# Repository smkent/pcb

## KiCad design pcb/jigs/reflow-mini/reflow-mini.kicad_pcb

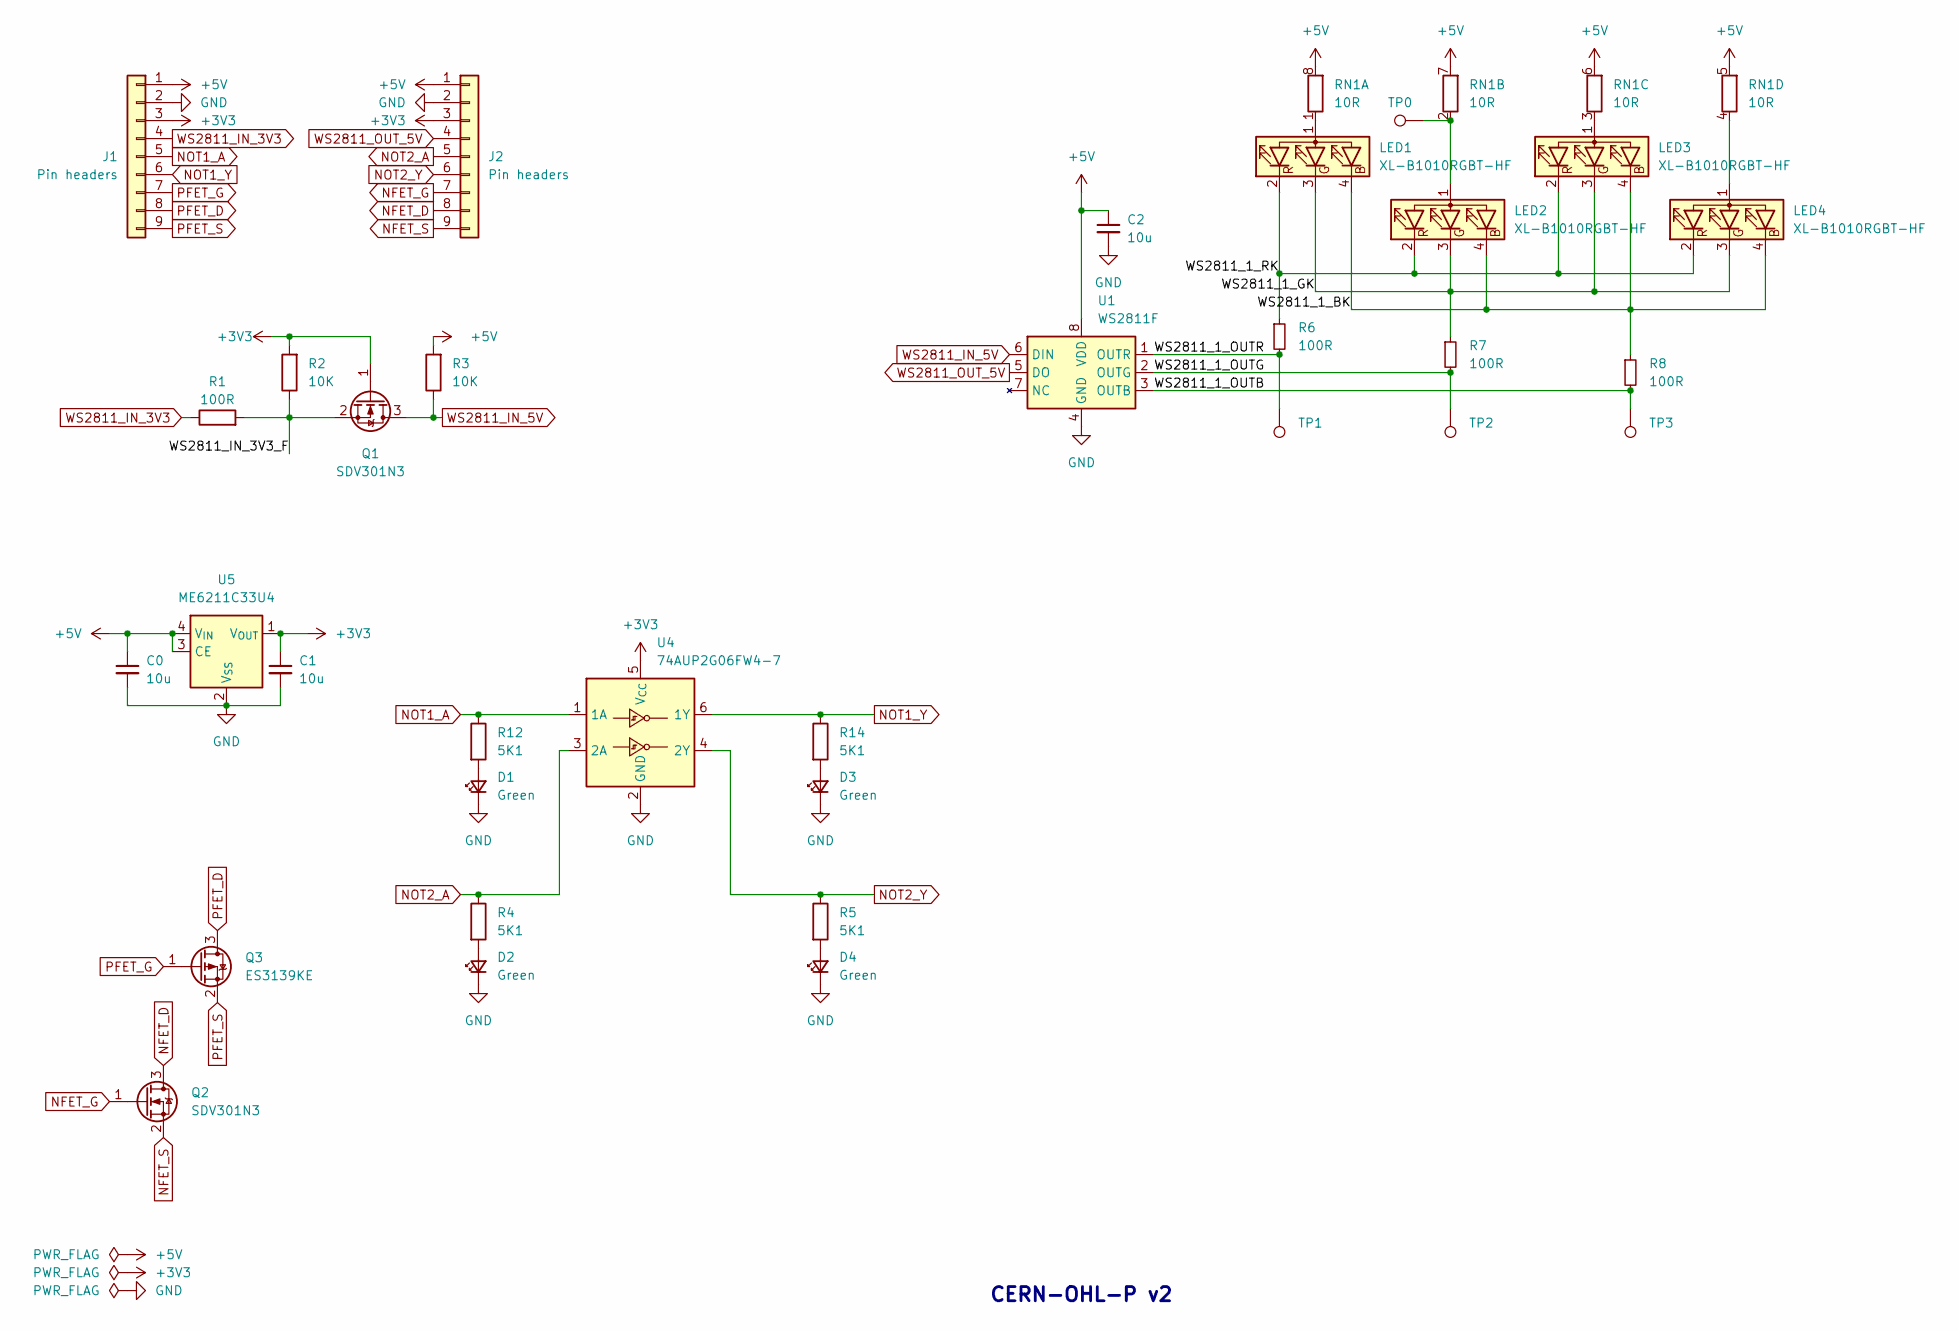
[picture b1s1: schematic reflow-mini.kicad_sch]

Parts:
C0, C1, C2: 10u; C_0402_1005Metric
D1, D2, D3, D4: Green; LED_0402_1005Metric
J1, J2: Pin headers; PinHeader_1x09_P2.54mm_Vertical_simple
LED1, LED2, LED3, LED4: XL-B1010RGBT-HF; LED_RGB_XL-B1010RGBT-HF_1.0x1.0mm; LCSC Part C22464515
Q1, Q2: SDV301N3; DFN1006-3; LCSC Part C5334596
Q3: ES3139KE; DFN1006-3; LCSC Part C7527987
R1: 100R; R_0402_1005Metric
R2, R3: 10K; R_0402_1005Metric
R4, R5, R12, R14: 5K1; R_0402_1005Metric
R6, R7, R8: 100R; R_0603_1608Metric
RN1: 10R; R_Array_Convex_4x0603
TP0, TP1, TP2, TP3: TestPoint; TestPoint_Pad_D1.0mm
U1: WS2811F; FSOP-8_3.3x1.7mm_P0.80mm; LCSC Part C5446692
U4: 74AUP2G06FW4-7; X2-DFN1010-6_L1.0-W1.0-P0.35-BL; LCSC Part C842402
U5: ME6211C33U4; UDFN-4-1EP_1x1mm_P0.65mm_EP0.48x0.48mm; LCSC Part C428904

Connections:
+3V3: C1.1, J1.3, J2.3, Q1.1 (G), R2.2, U4.5 (V_{CC}), U5.1 (V_{OUT})
+5V: C0.1, C2.1, J1.1, J2.1, R3.2, RN1.5 (R4.2), RN1.6 (R3.2), RN1.7 (R2.2), RN1.8 (R1.2), U1.8 (VDD), U5.3 (CE), U5.4 (V_{IN})
/WS2811_1_BK: LED1.4 (BK), LED2.4 (BK), LED3.4 (BK), LED4.4 (BK), R8.1
/WS2811_1_GK: LED1.3 (GK), LED2.3 (GK), LED3.3 (GK), LED4.3 (GK), R7.1
/WS2811_1_OUTB: R8.2, TP3.1, U1.3 (OUTB)
/WS2811_1_OUTG: R7.2, TP2.1, U1.2 (OUTG)
/WS2811_1_OUTR: R6.2, TP1.1, U1.1 (OUTR)
/WS2811_1_RK: LED1.2 (RK), LED2.2 (RK), LED3.2 (RK), LED4.2 (RK), R6.1
/WS2811_IN_3V3_F: Q1.2 (S), R1.2, R2.1
GND: C0.2, C1.2, C2.2, D1.1 (K), D2.1 (K), D3.1 (K), D4.1 (K), J1.2, J2.2, U1.4 (GND), U4.2 (GND), U5.2 (V_{SS})
NFET_D: J2.8, Q2.3 (D)
NFET_G: J2.7, Q2.1 (G)
NFET_S: J2.9, Q2.2 (S)
NOT1_A: J1.5, R12.1, U4.1 (1A)
NOT1_Y: J1.6, R14.1, U4.6 (1Y)
NOT2_A: J2.5, R4.1, U4.3 (2A)
NOT2_Y: J2.6, R5.1, U4.4 (2Y)
unnamed: D1.2 (A), R12.2
unnamed: D2.2 (A), R4.2
unnamed: D3.2 (A), R14.2
unnamed: D4.2 (A), R5.2
unnamed: LED1.1 (A), RN1.1 (R1.1)
unnamed: LED2.1 (A), RN1.2 (R2.1), TP0.1
unnamed: LED3.1 (A), RN1.3 (R3.1)
unnamed: LED4.1 (A), RN1.4 (R4.1)
PFET_D: J1.8, Q3.3 (D)
PFET_G: J1.7, Q3.1 (G)
PFET_S: J1.9, Q3.2 (S)
WS2811_IN_3V3: J1.4, R1.1
WS2811_IN_5V: Q1.3 (D), R3.1, U1.6 (DIN)
WS2811_OUT_5V: J2.4, U1.5 (DO)

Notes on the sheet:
CERN-OHL-P v2

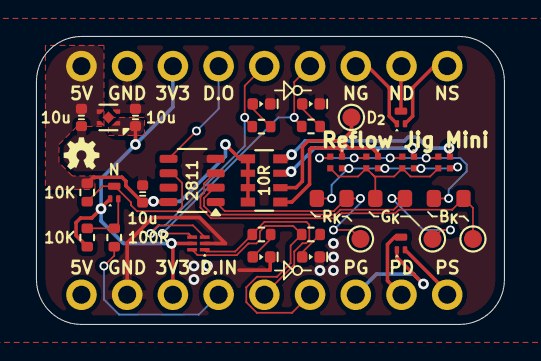
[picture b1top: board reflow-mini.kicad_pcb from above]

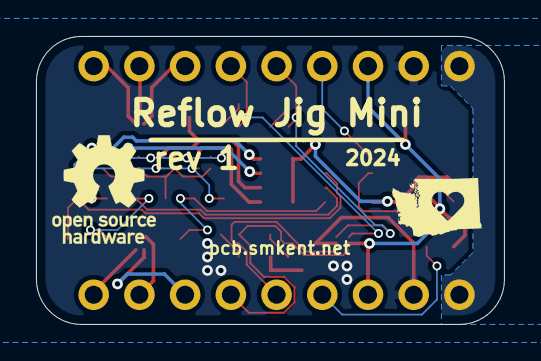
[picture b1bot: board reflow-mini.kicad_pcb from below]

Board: 2 copper layers, 26.0 x 16.0 mm, 34 parts (2 on the bottom side), 31 nets.

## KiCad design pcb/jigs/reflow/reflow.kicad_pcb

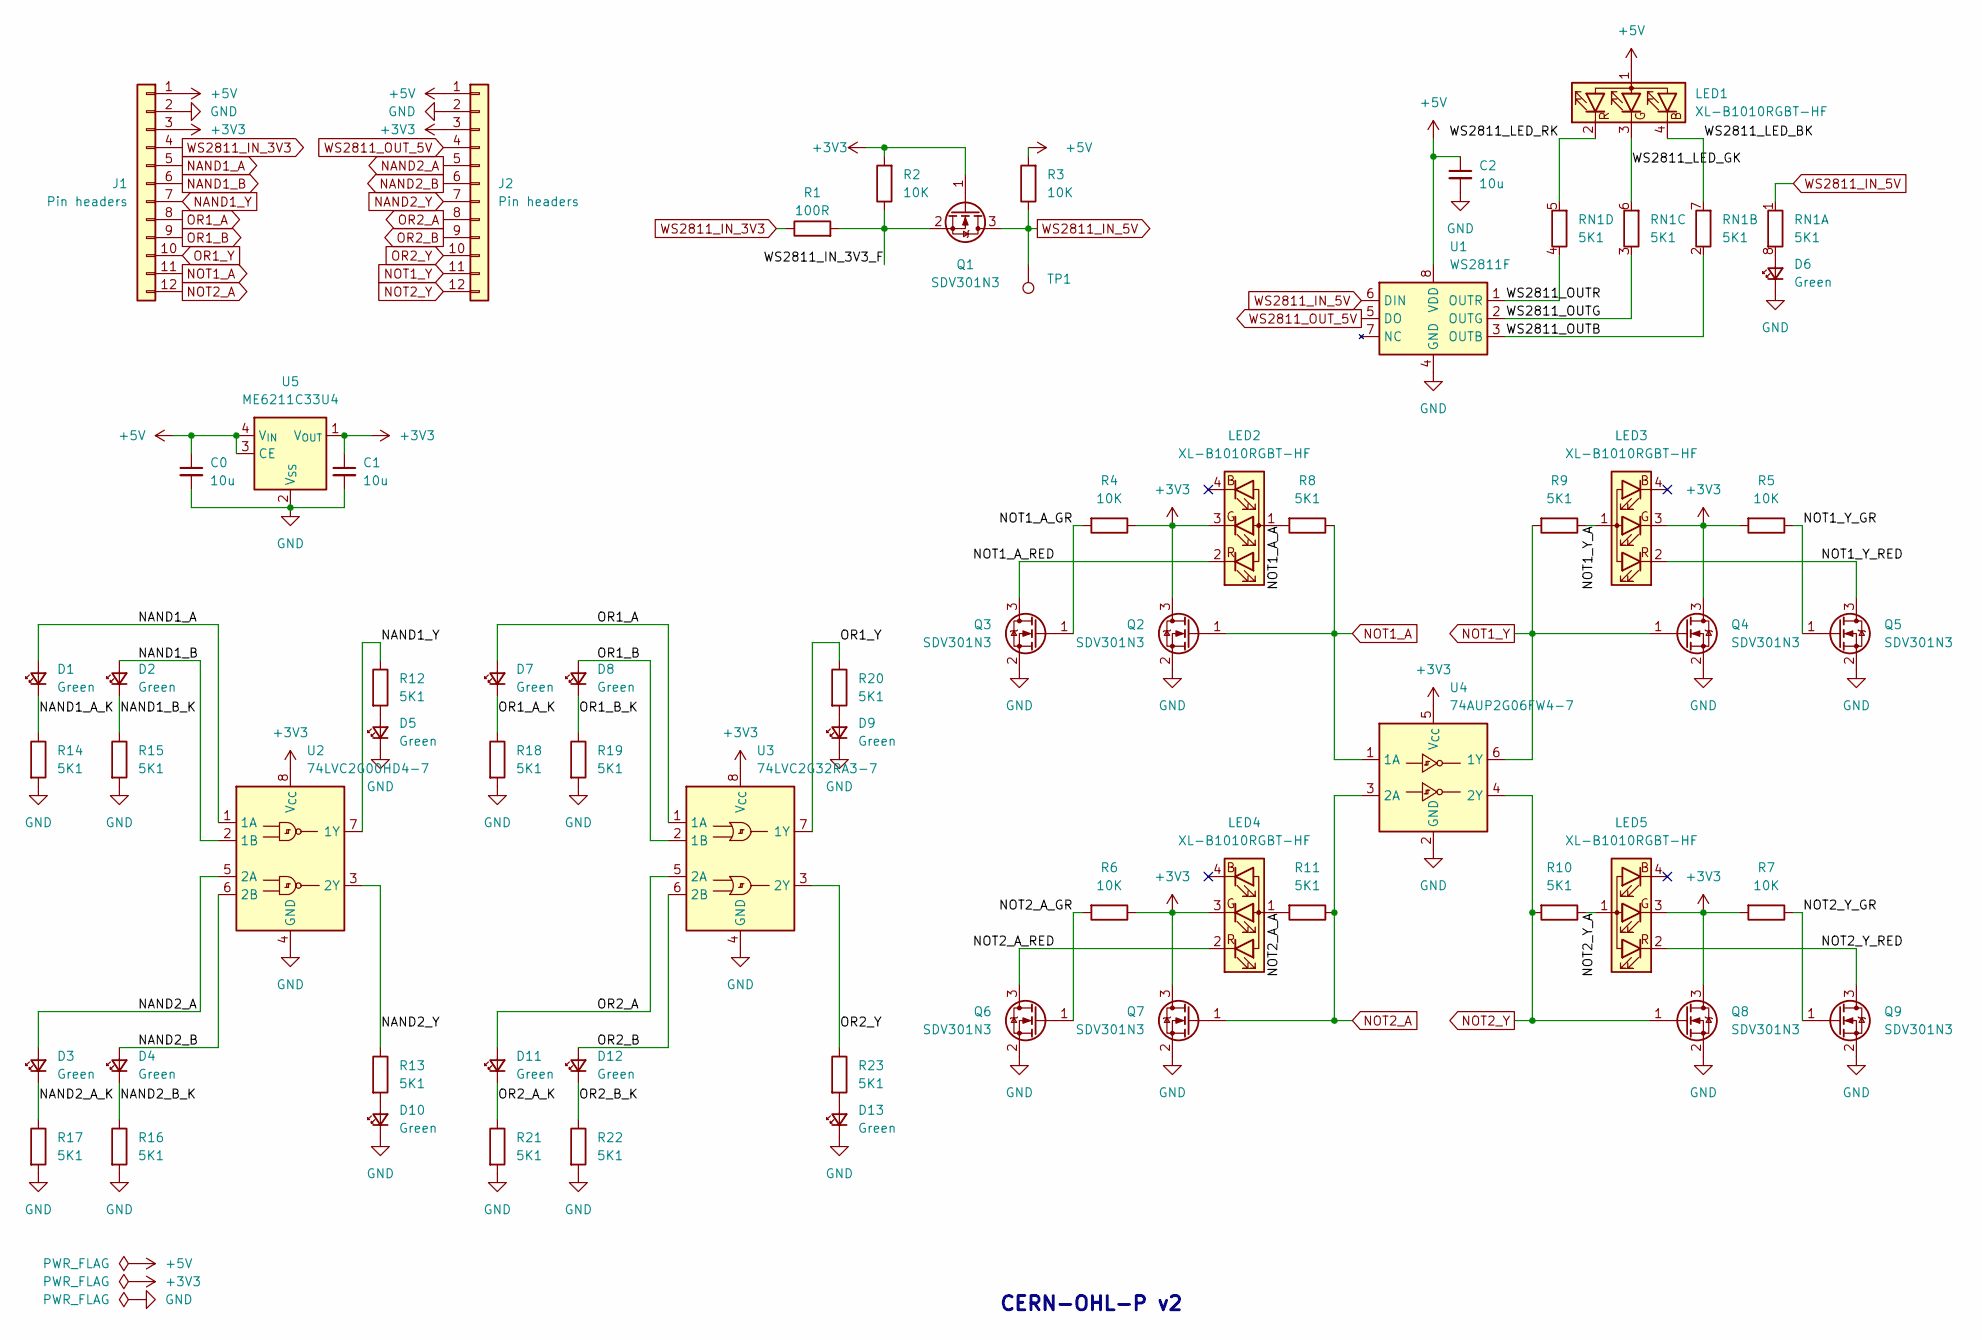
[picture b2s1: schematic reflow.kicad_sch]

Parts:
C0, C1, C2: 10u; C_0402_1005Metric
D1, D2, D3, D4, D5, D6, D7, D8, D9, D10, D11, D12, D13: Green; LED_0402_1005Metric
J1, J2: Pin headers; PinHeader_1x12_P2.54mm_Vertical_simple_pad2gnd
LED1, LED2, LED3, LED4, LED5: XL-B1010RGBT-HF; LED_RGB_XL-B1010RGBT-HF_1.0x1.0mm; LCSC Part C22464515
Q1, Q2, Q3, Q4, Q5, Q6, Q7, Q8, Q9: SDV301N3; DFN1006-3; LCSC Part C5334596
R1: 100R; R_0402_1005Metric
R2, R3, R4, R5, R6, R7: 10K; R_0402_1005Metric
R8, R9, R10, R11, R12, R13, R14, R15, R16, R17, R18, R19, R20, R21, R22, R23: 5K1; R_0402_1005Metric
RN1: 5K1; R_Array_Convex_4x0402
TP1: TestPoint; TestPoint_Pad_D1.0mm
U1: WS2811F; FSOP-8_3.3x1.7mm_P0.80mm; LCSC Part C5446692
U2: 74LVC2G00HD4-7; X2-DFN2010-8_L2.0-W1.0-P0.50-BL; LCSC Part C842639
U3: 74LVC2G32RA3-7; X2-DFN1210-8_L1.2-W1.0-P0.30-BL; LCSC Part C842616
U4: 74AUP2G06FW4-7; X2-DFN1010-6_L1.0-W1.0-P0.35-BL; LCSC Part C842402
U5: ME6211C33U4; UDFN-4-1EP_1x1mm_P0.65mm_EP0.48x0.48mm; LCSC Part C428904

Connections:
+3V3: C1.1, J1.3, J2.3, LED2.3 (GK), LED3.3 (GK), LED4.3 (GK), LED5.3 (GK), Q1.1 (G), Q2.3 (D), Q4.3 (D), Q7.3 (D), Q8.3 (D), R2.2, R4.1, R5.2, R6.1, R7.2, U2.8 (V_{CC}), U3.8 (V_{CC}), U4.5 (V_{CC}), U5.1 (V_{OUT})
+5V: C0.1, C2.1, J1.1, J2.1, LED1.1 (A), R3.2, U1.8 (VDD), U5.3 (CE), U5.4 (V_{IN})
/NAND1_A_K: D1.1 (K), R14.1
/NAND1_B_K: D2.1 (K), R15.1
/NAND2_A_K: D3.1 (K), R17.1
/NAND2_B_K: D4.1 (K), R16.1
/NOT1_A_A: LED2.1 (A), R8.2
/NOT1_A_GR: Q3.1 (G), R4.2
/NOT1_A_RED: LED2.2 (RK), Q3.3 (D)
/NOT1_Y_A: LED3.1 (A), R9.1
/NOT1_Y_GR: Q5.1 (G), R5.1
/NOT1_Y_RED: LED3.2 (RK), Q5.3 (D)
/NOT2_A_A: LED4.1 (A), R11.2
/NOT2_A_GR: Q6.1 (G), R6.2
/NOT2_A_RED: LED4.2 (RK), Q6.3 (D)
/NOT2_Y_A: LED5.1 (A), R10.1
/NOT2_Y_GR: Q9.1 (G), R7.1
/NOT2_Y_RED: LED5.2 (RK), Q9.3 (D)
/OR1_A_K: D7.1 (K), R18.1
/OR1_B_K: D8.1 (K), R19.1
/OR2_A_K: D11.1 (K), R21.1
/OR2_B_K: D12.1 (K), R22.1
/WS2811_IN_3V3_F: Q1.2 (S), R1.2, R2.1
/WS2811_LED_BK: LED1.4 (BK), RN1.7 (R2.2)
/WS2811_LED_GK: LED1.3 (GK), RN1.6 (R3.2)
/WS2811_LED_RK: LED1.2 (RK), RN1.5 (R4.2)
/WS2811_OUTB: RN1.2 (R2.1), U1.3 (OUTB)
/WS2811_OUTG: RN1.3 (R3.1), U1.2 (OUTG)
/WS2811_OUTR: RN1.4 (R4.1), U1.1 (OUTR)
GND: C0.2, C1.2, C2.2, D5.1 (K), D6.1 (K), D9.1 (K), D10.1 (K), D13.1 (K), J1.2, J2.2, Q2.2 (S), Q3.2 (S), Q4.2 (S), Q5.2 (S), Q6.2 (S), Q7.2 (S), Q8.2 (S), Q9.2 (S), R14.2, R15.2, R16.2, R17.2, R18.2, R19.2, R21.2, R22.2, U1.4 (GND), U2.4 (GND), U3.4 (GND), U4.2 (GND), U5.2 (V_{SS})
NAND1_A: D1.2 (A), J1.5, U2.1 (1A)
NAND1_B: D2.2 (A), J1.6, U2.2 (1B)
NAND1_Y: J1.7, R12.1, U2.7 (1Y)
NAND2_A: D3.2 (A), J2.5, U2.5 (2A)
NAND2_B: D4.2 (A), J2.6, U2.6 (2B)
NAND2_Y: J2.7, R13.1, U2.3 (2Y)
NOT1_A: J1.11, Q2.1 (G), R8.1, U4.1 (1A)
NOT1_Y: J2.11, Q4.1 (G), R9.2, U4.6 (1Y)
NOT2_A: J1.12, Q7.1 (G), R11.1, U4.3 (2A)
NOT2_Y: J2.12, Q8.1 (G), R10.2, U4.4 (2Y)
unnamed: D5.2 (A), R12.2
unnamed: D6.2 (A), RN1.8 (R1.2)
unnamed: D9.2 (A), R20.2
unnamed: D10.2 (A), R13.2
unnamed: D13.2 (A), R23.2
OR1_A: D7.2 (A), J1.8, U3.1 (1A)
OR1_B: D8.2 (A), J1.9, U3.2 (1B)
OR1_Y: J1.10, R20.1, U3.7 (1Y)
OR2_A: D11.2 (A), J2.8, U3.5 (2A)
OR2_B: D12.2 (A), J2.9, U3.6 (2B)
OR2_Y: J2.10, R23.1, U3.3 (2Y)
WS2811_IN_3V3: J1.4, R1.1
WS2811_IN_5V: Q1.3 (D), R3.1, RN1.1 (R1.1), TP1.1, U1.6 (DIN)
WS2811_OUT_5V: J2.4, U1.5 (DO)

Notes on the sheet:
CERN-OHL-P v2

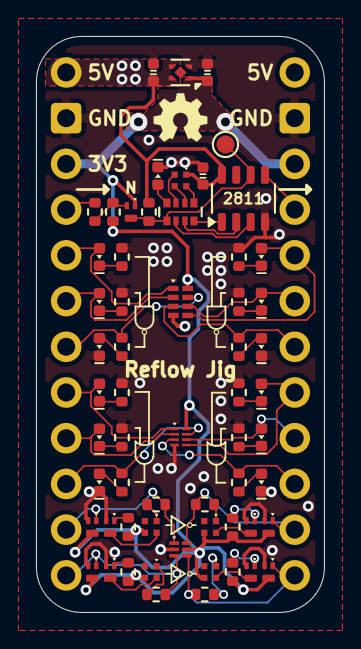
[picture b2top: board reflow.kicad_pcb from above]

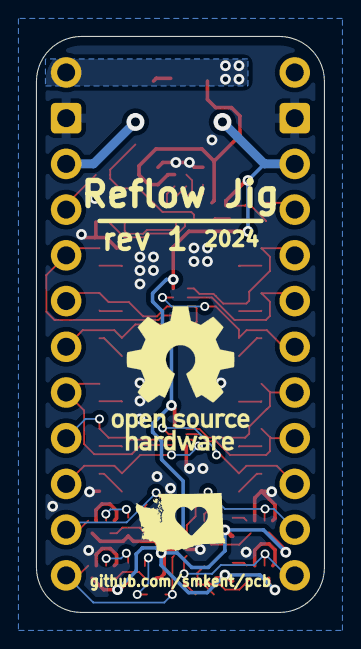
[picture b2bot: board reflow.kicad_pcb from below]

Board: 2 copper layers, 16.0 x 32.0 mm, 62 parts (2 on the bottom side), 54 nets.

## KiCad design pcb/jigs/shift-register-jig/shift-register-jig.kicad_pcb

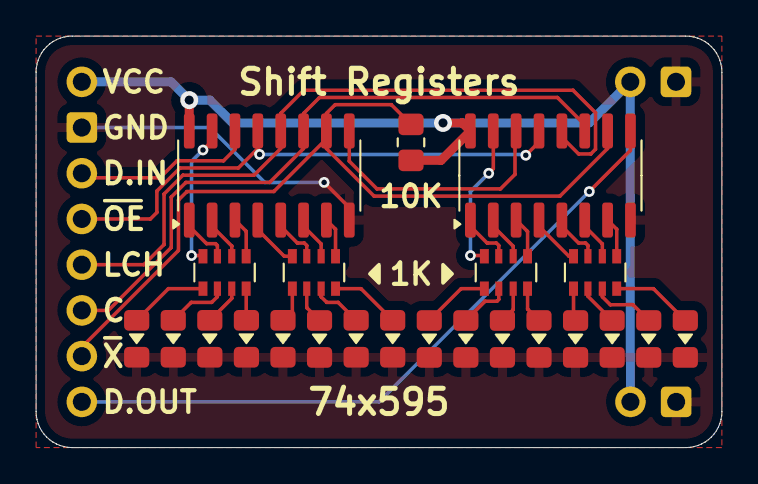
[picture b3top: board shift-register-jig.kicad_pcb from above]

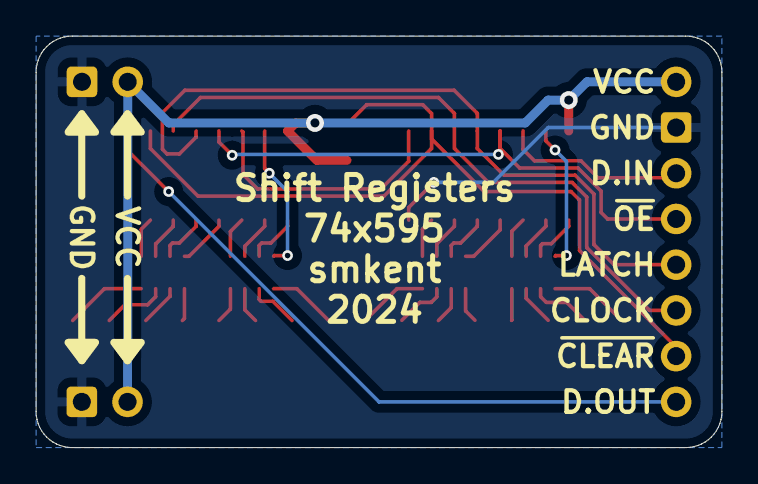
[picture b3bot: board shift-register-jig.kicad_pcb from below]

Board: 2 copper layers, 38.1 x 22.9 mm, 26 parts (3 on the bottom side), 41 nets.

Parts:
J1, J5: Conn_01x02; PinHeader_1x02_P2.54mm_Vertical_simple_pad2gnd
J2: Conn_01x08; PinHeader_1x08_P2.54mm_Vertical_simple_pad2gnd
LED1, LED2, LED3, LED4, LED5, LED6, LED7, LED8, LED9, LED10, LED11, LED12, LED13, LED14, LED15, LED16: LED; LED_0805_2012Metric_Pad1.15x1.40mm_HandSolder_simple
R1: 10K; R_0805_2012Metric_Pad1.20x1.40mm_HandSolder
RN1, RN2, RN3, RN4: 1K; R_Array_Convex_4x0603
U1, U2: 74HC595; SOIC-16_3.9x9.9mm_P1.27mm

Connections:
Clear: J2.7, R1.2, U1.10 (~SRCLR), U2.10 (~SRCLR)
Clock: J2.6, U1.11 (SRCLK), U2.11 (SRCLK)
Data: J2.3, U1.14 (SER)
Data2: U1.9 (QH'), U2.14 (SER)
Data_Out: J2.8, U2.9 (QH')
GND: J1.2, J2.2, J5.2, LED1.1 (K), LED2.1 (K), LED3.1 (K), LED4.1 (K), LED5.1 (K), LED6.1 (K), LED7.1 (K), LED8.1 (K), LED9.1 (K), LED10.1 (K), LED11.1 (K), LED12.1 (K), LED13.1 (K), LED14.1 (K), LED15.1 (K), LED16.1 (K), U1.8 (GND), U2.8 (GND)
LED1: RN1.8 (R1.2), U1.15 (QA)
LED2: RN1.7 (R2.2), U1.1 (QB)
LED3: RN1.6 (R3.2), U1.2 (QC)
LED4: RN1.5 (R4.2), U1.3 (QD)
LED5: RN2.8 (R1.2), U1.4 (QE)
LED6: RN2.7 (R2.2), U1.5 (QF)
LED7: RN2.6 (R3.2), U1.6 (QG)
LED8: RN2.5 (R4.2), U1.7 (QH)
LED9: RN3.8 (R1.2), U2.15 (QA)
LED10: RN3.7 (R2.2), U2.1 (QB)
LED11: RN3.6 (R3.2), U2.2 (QC)
LED12: RN3.5 (R4.2), U2.3 (QD)
LED13: RN4.8 (R1.2), U2.4 (QE)
LED14: RN4.7 (R2.2), U2.5 (QF)
LED15: RN4.6 (R3.2), U2.6 (QG)
LED16: RN4.5 (R4.2), U2.7 (QH)
Latch: J2.5, U1.12 (RCLK), U2.12 (RCLK)
unnamed: LED1.2 (A), RN1.1 (R1.1)
unnamed: LED2.2 (A), RN1.2 (R2.1)
unnamed: LED3.2 (A), RN1.3 (R3.1)
unnamed: LED4.2 (A), RN1.4 (R4.1)
unnamed: LED5.2 (A), RN2.1 (R1.1)
unnamed: LED6.2 (A), RN2.2 (R2.1)
unnamed: LED7.2 (A), RN2.3 (R3.1)
unnamed: LED8.2 (A), RN2.4 (R4.1)
unnamed: LED9.2 (A), RN3.1 (R1.1)
unnamed: LED10.2 (A), RN3.2 (R2.1)
unnamed: LED11.2 (A), RN3.3 (R3.1)
unnamed: LED12.2 (A), RN3.4 (R4.1)
unnamed: LED13.2 (A), RN4.1 (R1.1)
unnamed: LED14.2 (A), RN4.2 (R2.1)
unnamed: LED15.2 (A), RN4.3 (R3.1)
unnamed: LED16.2 (A), RN4.4 (R4.1)
OE: J2.4, U1.13 (~OE), U2.13 (~OE)
VCC: J1.1, J2.1, J5.1, R1.1, U1.16 (VCC), U2.16 (VCC)

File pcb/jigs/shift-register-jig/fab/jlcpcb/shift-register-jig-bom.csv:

Comment,Designator,Footprint,LCSC
LED,"LED1,LED2,LED3,LED4,LED5,LED6,LED7,LED8,LED9,LED10,LED11,LED12,LED13,LED14,LED15,LED16",custom:LED_0805_2012Metric_Pad1.15x1.40mm_HandSolder_simple,
Conn_01x02,"J1,J5",custom:PinHeader_1x02_P2.54mm_Vertical_simple_pad2gnd,
1K,"RN1,RN2,RN3,RN4",Resistor_SMD:R_Array_Convex_4x0603,
74HC595,"U1,U2",Package_SO:SOIC-16_3.9x9.9mm_P1.27mm,
10K,R1,Resistor_SMD:R_0805_2012Metric_Pad1.20x1.40mm_HandSolder,
Conn_01x08,J2,custom:PinHeader_1x08_P2.54mm_Vertical_simple_pad2gnd,

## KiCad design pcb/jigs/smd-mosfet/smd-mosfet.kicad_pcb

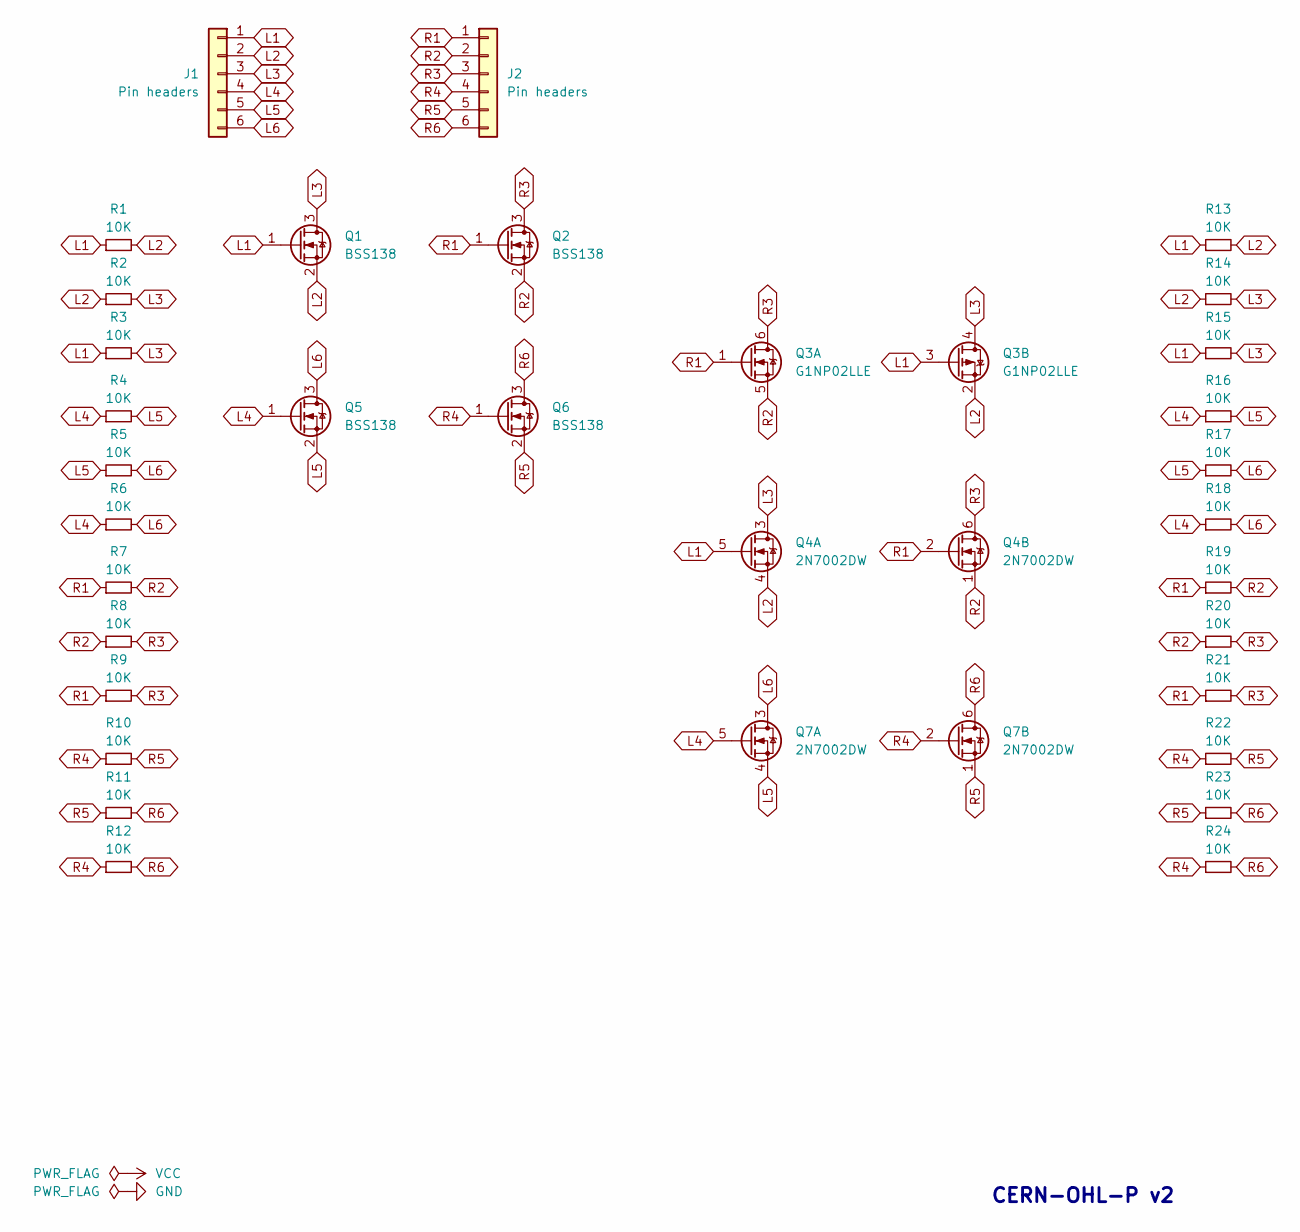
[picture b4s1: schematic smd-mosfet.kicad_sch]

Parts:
J1, J2: Pin headers; PinHeader_1x06_P2.54mm_Vertical_slim_simple
Q1, Q2, Q5, Q6: BSS138; SOT-23_mosfet
Q3: G1NP02LLE; SOT-23-6_G1NP02LLE_mosfet; LCSC Part C7465318
Q4, Q7: 2N7002DW; SOT-363_SC-70-6_mosfet; LCSC Part C5190214
R1, R2, R3, R4, R5, R6, R7, R8, R9, R10, R11, R12, R13, R14, R15, R16, R17, R18, R19, R20, R21, R22, R23, R24: 10K; R_0603_1608Metric_Pad0.98x0.95mm_HandSolder_simple

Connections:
L1: J1.1, Q1.1 (G), Q3.3 (G), Q4.5 (G), R1.1, R3.1, R13.1, R15.1
L2: J1.2, Q1.2 (S), Q3.2 (S), Q4.4 (S), R1.2, R2.1, R13.2, R14.1
L3: J1.3, Q1.3 (D), Q3.4 (D), Q4.3 (D), R2.2, R3.2, R14.2, R15.2
L4: J1.4, Q5.1 (G), Q7.5 (G), R4.1, R6.1, R16.1, R18.1
L5: J1.5, Q5.2 (S), Q7.4 (S), R4.2, R5.1, R16.2, R17.1
L6: J1.6, Q5.3 (D), Q7.3 (D), R5.2, R6.2, R17.2, R18.2
R1: J2.1, Q2.1 (G), Q3.1 (G), Q4.2 (G), R7.1, R9.1, R19.1, R21.1
R2: J2.2, Q2.2 (S), Q3.5 (S), Q4.1 (S), R7.2, R8.1, R19.2, R20.1
R3: J2.3, Q2.3 (D), Q3.6 (D), Q4.6 (D), R8.2, R9.2, R20.2, R21.2
R4: J2.4, Q6.1 (G), Q7.2 (G), R10.1, R12.1, R22.1, R24.1
R5: J2.5, Q6.2 (S), Q7.1 (S), R10.2, R11.1, R22.2, R23.1
R6: J2.6, Q6.3 (D), Q7.6 (D), R11.2, R12.2, R23.2, R24.2

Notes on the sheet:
CERN-OHL-P v2

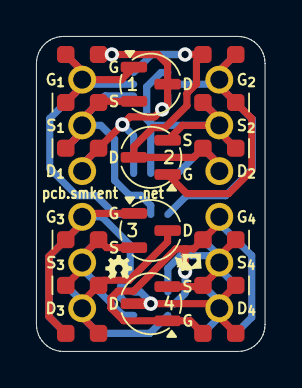
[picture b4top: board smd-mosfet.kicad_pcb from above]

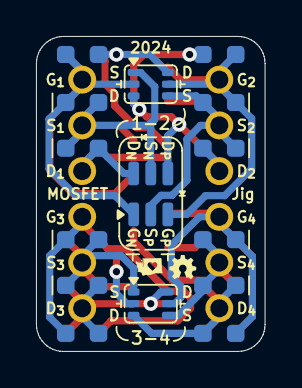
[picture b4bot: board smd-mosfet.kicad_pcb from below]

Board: 2 copper layers, 12.7 x 17.5 mm, 33 parts (17 on the bottom side), 12 nets.

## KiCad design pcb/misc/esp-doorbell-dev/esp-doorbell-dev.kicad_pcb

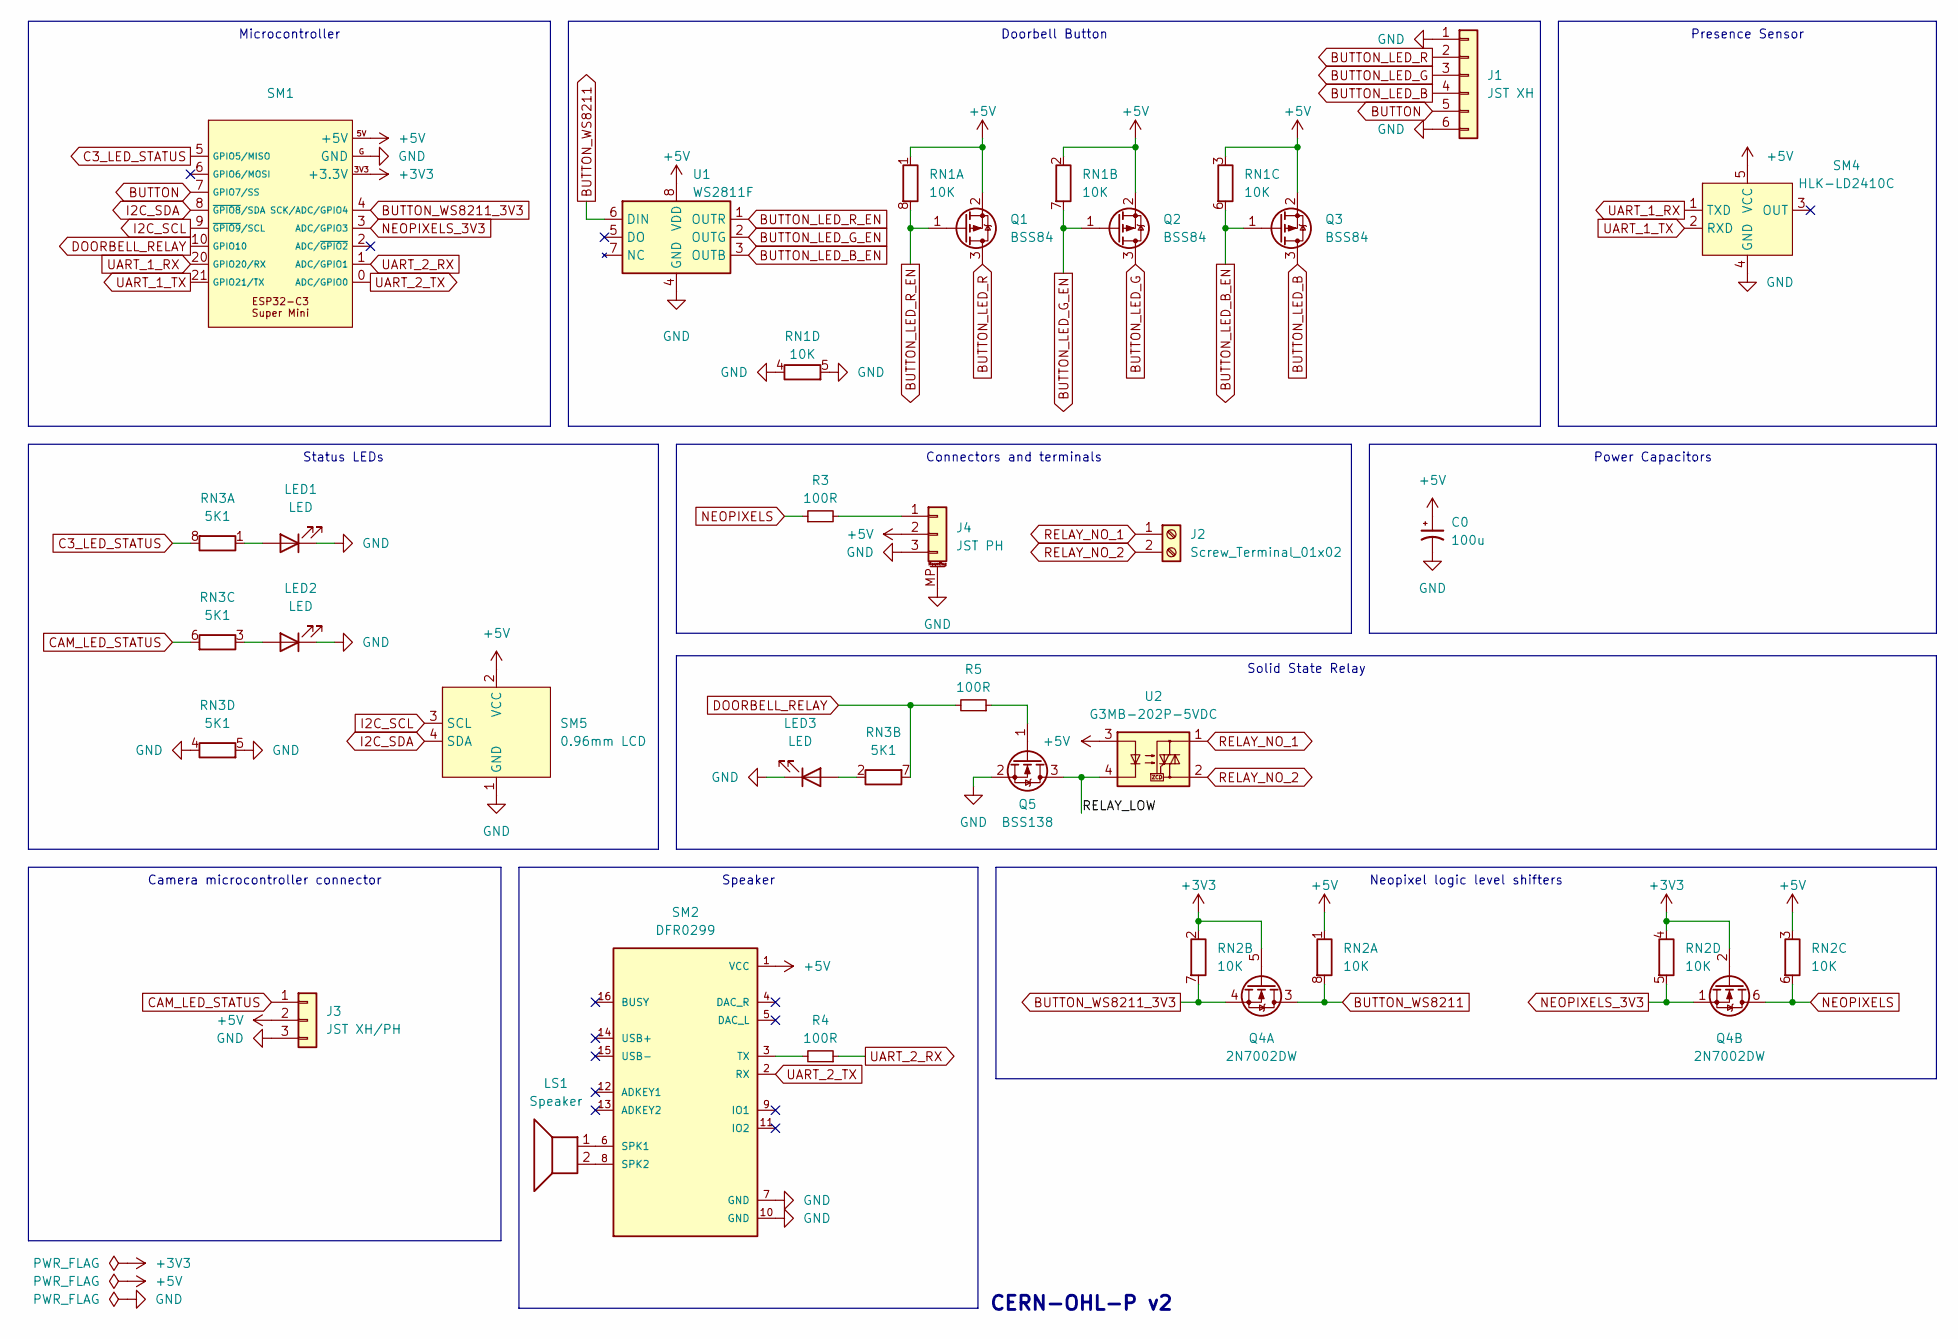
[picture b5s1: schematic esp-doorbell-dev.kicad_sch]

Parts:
C0: 100u; CP_Elec_5x5.4
J1: JST XH; JST_XH_S6B-XH-2AW_1x06_P2.50mm_Horizontal
J2: Screw_Terminal_01x02; TerminalBlock_Phoenix_PT-1,5-2-3.5-H_1x02_P3.50mm_Horizontal
J3: JST XH/PH; Conn_Combo_JST-1x03-XH_PH-THT
J4: JST PH; STEMMA-Signal-SMD-horizontal
LED1, LED2, LED3: LED; LED_0603_1608Metric_Pad1.05x0.95mm_HandSolder_simple
LS1: Speaker; Conn_Combo_JST-1x02-XH_PH-SMD-pad2gnd
Q1, Q2, Q3: BSS84; SOT-23
Q4: 2N7002DW; SOT-363_SC-70-6_HandSolder; LCSC Part C5190214
Q5: BSS138; SOT-23
R3, R4, R5: 100R; R_0603_1608Metric_Pad0.98x0.95mm_HandSolder
RN1, RN2: 10K; R_Array_Convex_4x0603
RN3: 5K1; R_Array_Convex_4x0603
SM1: ESP32-C3-Super-Mini-Pins
SM2: DFR0299; DFPlayer-Mini-DFR0299-module
SM4: HLK-LD2410C; HLK-LD2410C-module; LCSC Part C19723500
SM5: 0.96mm LCD; LCD-OLED-0.96-module-noholes; LCSC Part C7465997
U1: WS2811F; FSOP-8_3.3x1.7mm_P0.80mm; LCSC Part C5446692
U2: G3MB-202P-5VDC; Relay_G3MB-202P

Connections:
+3V3: Q4.2 (G), Q4.5 (G), RN2.2 (R2.1), RN2.4 (R4.1), SM1.3V3 (+3.3V)
+5V: C0.1, J3.2, J4.2, Q1.2 (S), Q2.2 (S), Q3.2 (S), RN1.1 (R1.1), RN1.2 (R2.1), RN1.3 (R3.1), RN2.1 (R1.1), RN2.3 (R3.1), SM1.5V (+5V), SM2.1 (VCC), SM4.5 (VCC), SM5.2 (VCC), U1.8 (VDD), U2.3
/RELAY_LOW: Q5.3 (D), U2.4
BUTTON: J1.5, SM1.7 (GPIO7/SS)
BUTTON_LED_B: J1.4, Q3.3 (D)
BUTTON_LED_B_EN: Q3.1 (G), RN1.6 (R3.2), U1.3 (OUTB)
BUTTON_LED_G: J1.3, Q2.3 (D)
BUTTON_LED_G_EN: Q2.1 (G), RN1.7 (R2.2), U1.2 (OUTG)
BUTTON_LED_R: J1.2, Q1.3 (D)
BUTTON_LED_R_EN: Q1.1 (G), RN1.8 (R1.2), U1.1 (OUTR)
BUTTON_WS8211: Q4.3 (D), RN2.8 (R1.2), U1.6 (DIN)
BUTTON_WS8211_3V3: Q4.4 (S), RN2.7 (R2.2), SM1.4 (SCK/ADC/GPIO4)
C3_LED_STATUS: RN3.8 (R1.2), SM1.5 (GPIO5/MISO)
CAM_LED_STATUS: J3.1, RN3.6 (R3.2)
DOORBELL_RELAY: R5.2, RN3.7 (R2.2), SM1.10 (GPIO10)
GND: C0.2, J1.1, J1.6, J3.3, J4.3, J4.MP (MountPin), LED1.1 (K), LED2.1 (K), LED3.1 (K), Q5.2 (S), RN1.4 (R4.1), RN1.5 (R4.2), RN3.4 (R4.1), RN3.5 (R4.2), SM1.G (GND), SM2.7 (GND), SM2.10 (GND), SM4.4 (GND), SM5.1 (GND), U1.4 (GND)
I2C_SCL: SM1.9 (~GPIO9/SCL), SM5.3 (SCL)
I2C_SDA: SM1.8 (~GPIO8/SDA), SM5.4 (SDA)
NEOPIXELS: Q4.6 (D), R3.1, RN2.6 (R3.2)
NEOPIXELS_3V3: Q4.1 (S), RN2.5 (R4.2), SM1.3 (ADC/GPIO3)
unnamed: J4.1, R3.2
unnamed: LED1.2 (A), RN3.1 (R1.1)
unnamed: LED2.2 (A), RN3.3 (R3.1)
unnamed: LED3.2 (A), RN3.2 (R2.1)
unnamed: Q5.1 (G), R5.1
unnamed: LS1.1, SM2.6 (SPK1)
unnamed: LS1.2, SM2.8 (SPK2)
unnamed: R4.2, SM2.3 (TX)
RELAY_NO_1: J2.1, U2.1
RELAY_NO_2: J2.2, U2.2
UART_1_RX: SM1.20 (GPIO20/RX), SM4.1 (TXD)
UART_1_TX: SM1.21 (GPIO21/TX), SM4.2 (RXD)
UART_2_RX: R4.1, SM1.1 (ADC/GPIO1)
UART_2_TX: SM1.0 (ADC/GPIO0), SM2.2 (RX)

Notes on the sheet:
Microcontroller
Doorbell Button
Presence Sensor
Camera microcontroller connector
Status LEDs
Power Capacitors
Solid State Relay
Speaker
Neopixel logic level shifters
Connectors and terminals
CERN-OHL-P v2

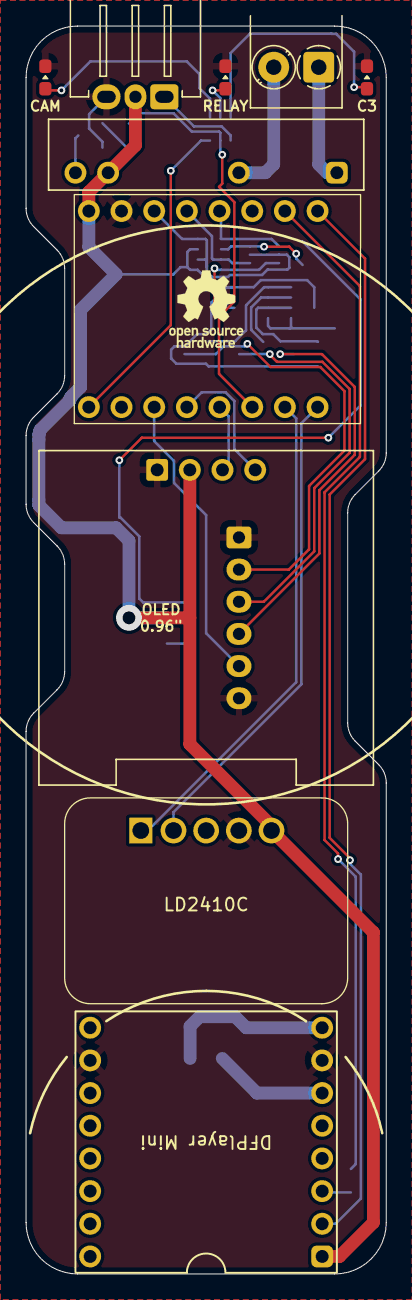
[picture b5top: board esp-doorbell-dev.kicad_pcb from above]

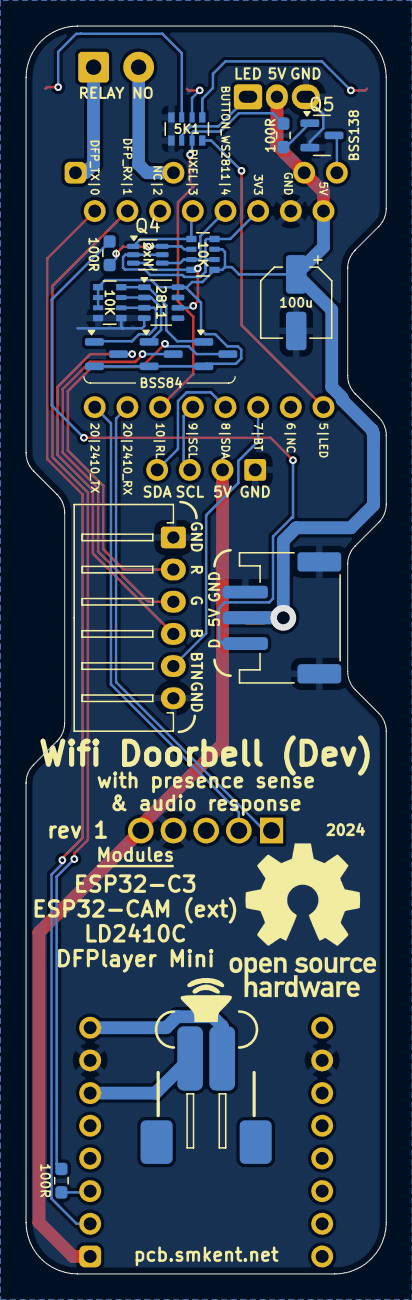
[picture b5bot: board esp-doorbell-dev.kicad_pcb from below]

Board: 2 copper layers, 28.0 x 97.0 mm, 26 parts (16 on the bottom side), 34 nets.

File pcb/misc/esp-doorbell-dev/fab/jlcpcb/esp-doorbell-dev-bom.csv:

Comment,Designator,Footprint,LCSC
BSS84,"Q1,Q2,Q3",custom:SOT-23_simple,
G3MB-202P-5VDC,U2,custom:RELAY-G3MB-202P-5VDC,
10K,"RN1,RN2",Resistor_SMD:R_Array_Convex_4x0603,
100R,"R3,R4,R5",custom:R_0603_1608Metric_Pad0.98x0.95mm_HandSolder_simple,
5K1,RN3,Resistor_SMD:R_Array_Convex_4x0603,
0.96mm LCD,SM5,modules:LCD-OLED-0.96-module-noholes,C7465997
BSS138,Q5,custom:SOT-23_simple,
HLK-LD2410C-P,SM4,lcsc:SENSOR-TH_HLK-LD2410C-P,C19723500
DFR0299,SM2,modules:DFPlayer-Mini-DFR0299-module,
Speaker,LS1,custom:Conn_Combo_JST-1x02-XH_PH-SMD-pad2gnd,
JST XH/PH,J3,custom:Conn_Combo_JST-1x03-XH_PH-THT,
2N7002DW,Q4,custom:SOT-363_SC-70-6_simple,C5190214
LED,"LED1,LED2,LED3",custom:LED_0603_1608Metric_Pad1.05x0.95mm_HandSolder_simple,
100u,C0,Capacitor_SMD:CP_Elec_5x5.4,
JST PH,J4,connectors:STEMMA-Signal-SMD-horizontal,
Screw_Terminal_01x02,J2,"custom:TerminalBlock_Phoenix_PT-1,5-2-3.5-H_1x02_P3.50mm_Horizontal_custom",
WS2811F,U1,lcsc:FSOP-8_L3.3-W1.7-P0.80-LS2.9-BL,C5446692
JST XH,J1,custom:JST_XH_S6B-XH_1x06_P2.50mm_Horizontal,
~,SM1,modules:ESP32-C3-Super-Mini-Pins,
